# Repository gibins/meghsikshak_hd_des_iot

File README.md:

# Hardware Design and Development for Embedded Systems and Internet of Things

#Module 1
#Module 2
#Module 3
#Module 4

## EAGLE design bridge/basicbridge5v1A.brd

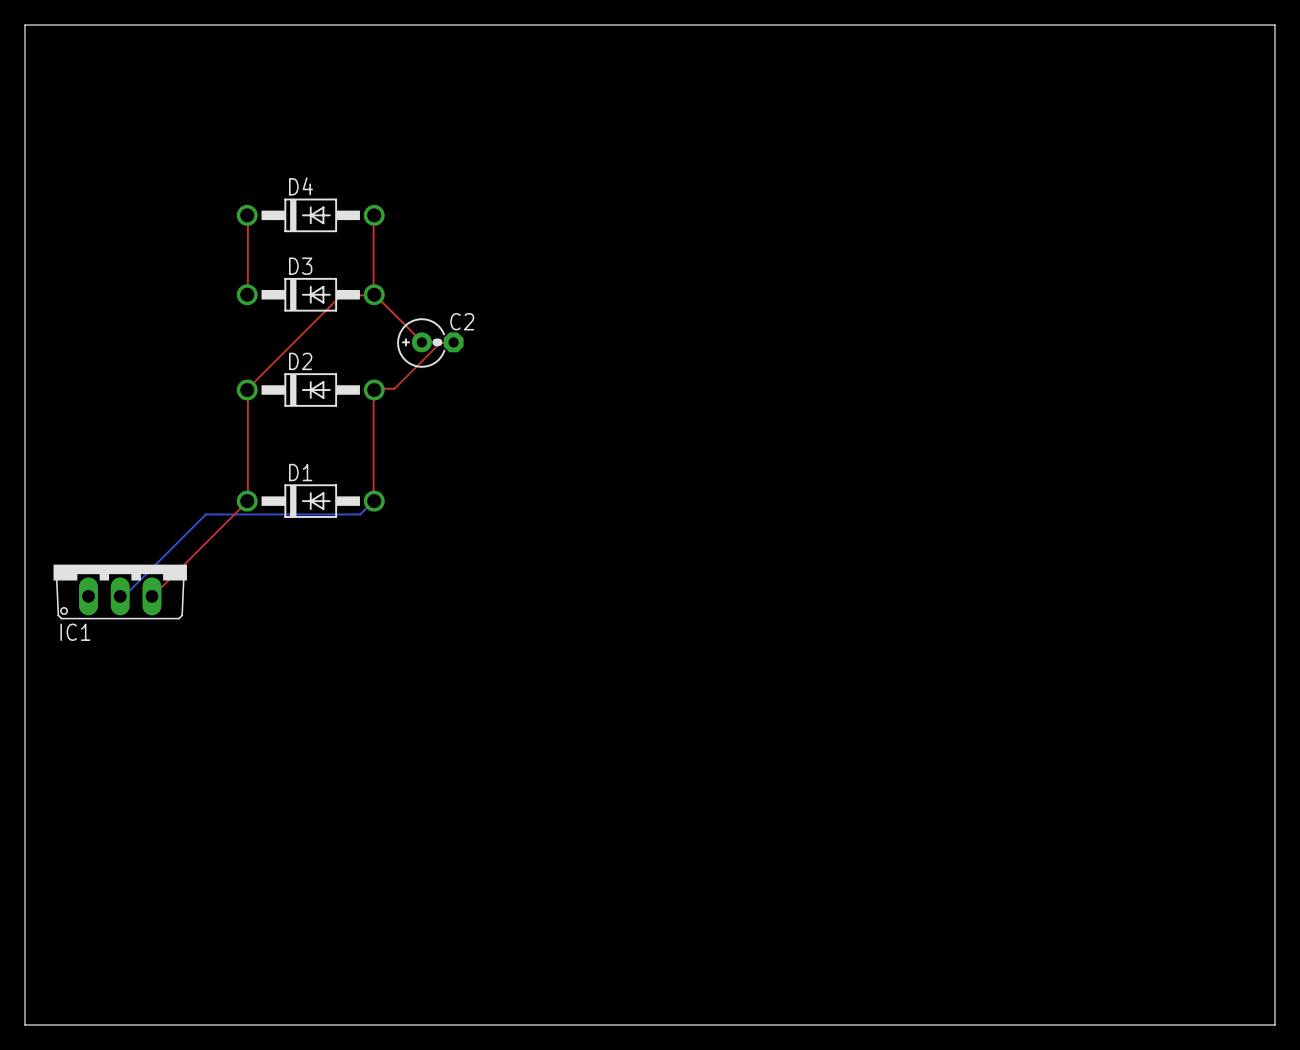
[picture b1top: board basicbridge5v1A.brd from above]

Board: 2 copper layers, 100.0 x 80.0 mm, 6 parts (0 on the bottom side), 3 nets.

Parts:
C2: E2,5-4R
D1, D2, D3, D4: 1N4004; DO41-10
IC1: 7805TV; TO220V

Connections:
GND: C2.-, D1.A, D2.A, IC1.2
unnamed: D3.C, D4.C, IC1.1
VCC: C2.+, D1.C, D2.C, D3.A, D4.A, IC1.3

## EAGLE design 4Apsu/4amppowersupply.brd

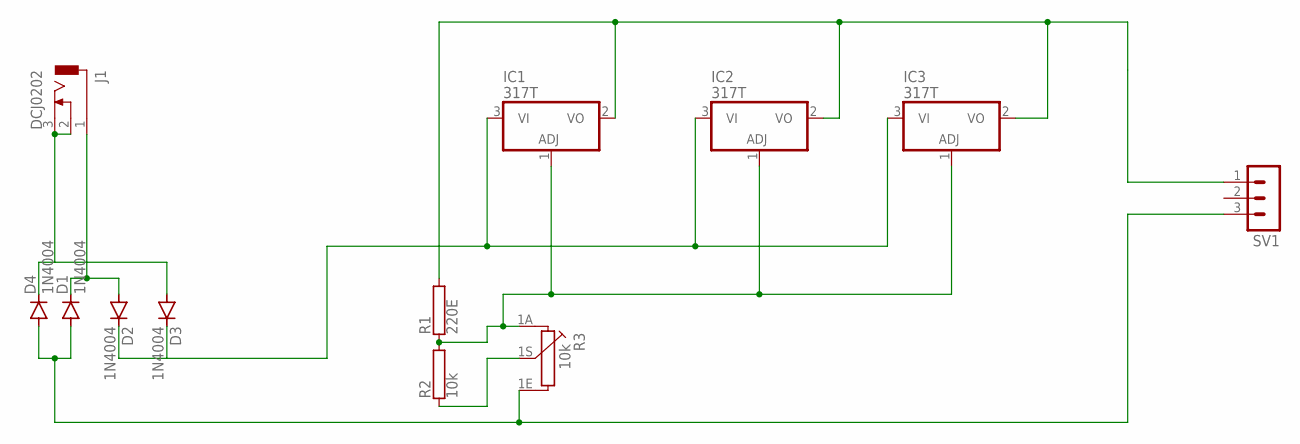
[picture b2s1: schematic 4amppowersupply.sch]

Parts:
D1, D2, D3, D4: 1N4004; DO41-10
IC1, IC2, IC3: 317T; TO220H
J1: DCJ0202
R1: 220E; TO-247-2V
R2: 10k; TO-247-2V
R3: 10k; PC16S
SV1: MA03-1

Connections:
unnamed: D3.A, D4.C, J1.2, J1.3
unnamed: D1.C, D2.A, J1.1
unnamed: D1.A, D4.A, R3.1E, SV1.3
unnamed: D2.C, D3.C, IC1.3 (VI), IC2.3 (VI), IC3.3 (VI)
unnamed: IC1.1 (ADJ), IC2.1 (ADJ), IC3.1 (ADJ), R1.1, R2.2, R3.1A
unnamed: R2.1, R3.1S
unnamed: IC1.2 (VO), IC2.2 (VO), IC3.2 (VO), R1.2, SV1.1

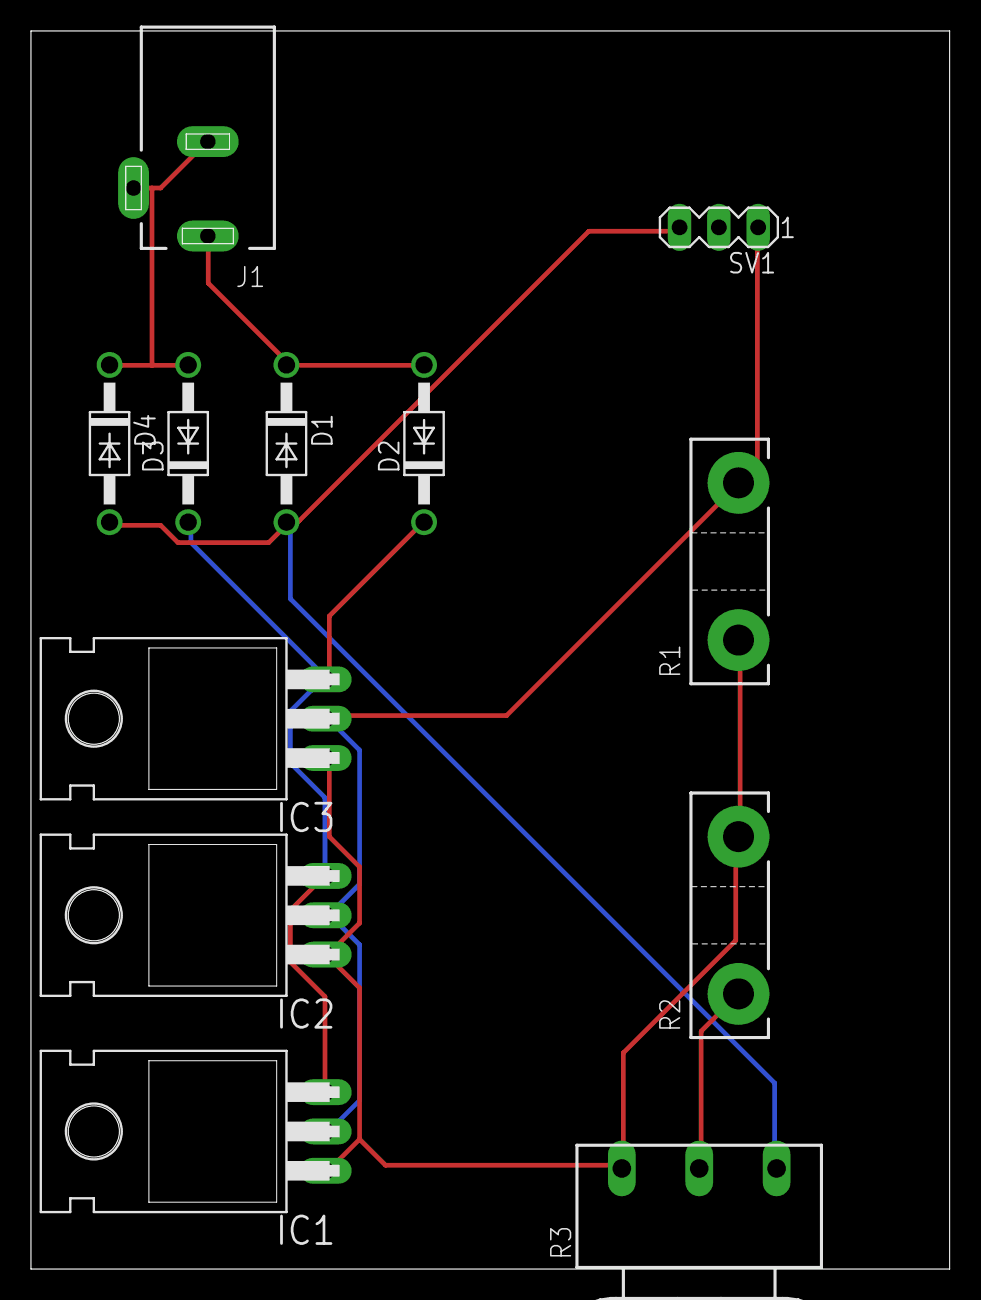
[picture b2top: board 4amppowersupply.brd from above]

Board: 2 copper layers, 59.4 x 80.0 mm, 12 parts (0 on the bottom side), 7 nets.

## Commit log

2021-10-31 Initial Commit- ReadMe updated
2021-10-31 test commit
2021-10-31 Assignment 1 Question updated
2021-11-19 first assignment partial
2021-11-24 basic setup
